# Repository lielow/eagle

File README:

Eagle file for IOT Project.

15/07/2559

Tong.

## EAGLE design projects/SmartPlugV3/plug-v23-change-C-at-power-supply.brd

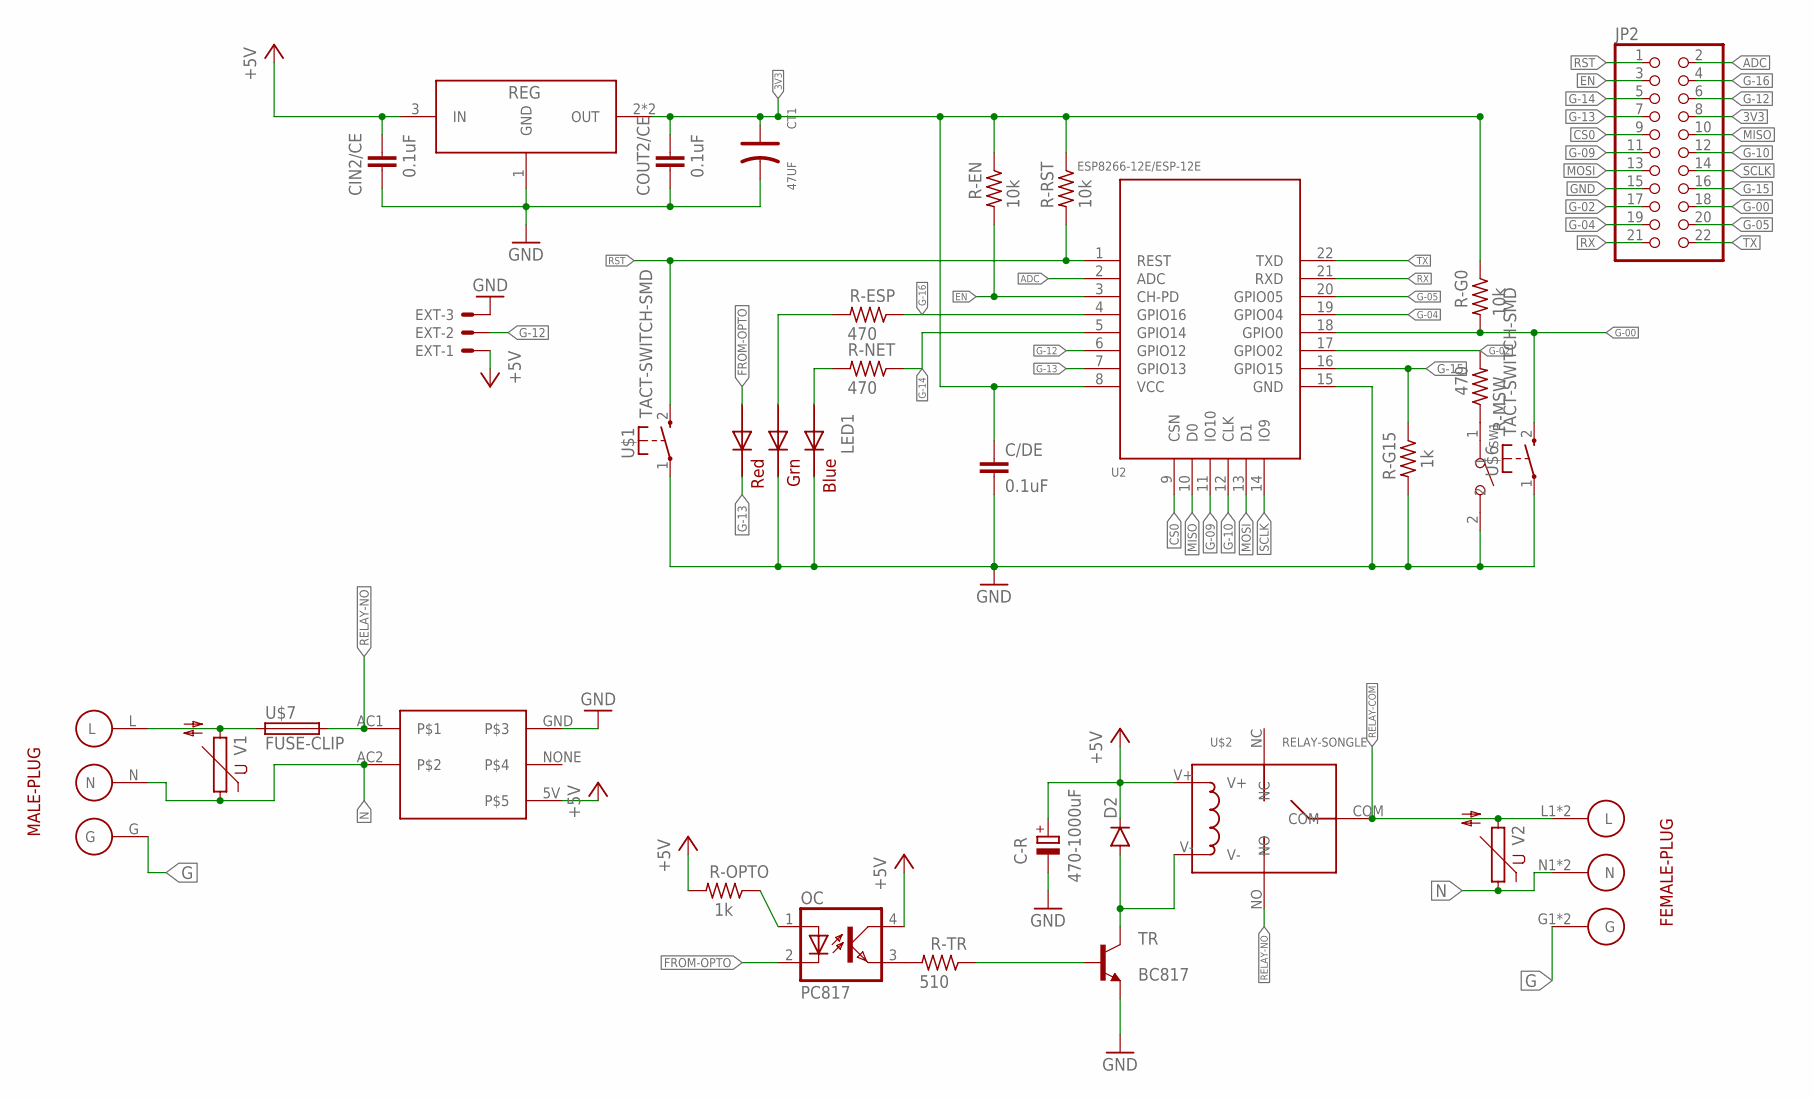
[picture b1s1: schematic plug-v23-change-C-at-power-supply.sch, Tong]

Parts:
C-R: 470-1000uF; E3,5-8
C/DE: 0.1uF; C0805
CIN2/CE: 0.1uF; C0805K
COUT2/CE: 0.1uF; C0805K
CT1: 47UF; ELECTRO-SMD-C-6MM
D2: DIODESOD123; SOD-123
EXT: 53048-03
JP2: PINHD-2X11; 2X11
LED1: RGBLED5050
OC: PC817; DIL04
R-EN: 10k; M0805
R-ESP: 470; M0805
R-G0: 10k; M0805
R-G15: 1k; M0805
R-MSW: 470; M0805
R-NET: 470; M0805
R-OPTO: 1k; M0805
R-RST: 10k; M0805
R-TR: 510; M0805
REG: AMS1117-3.3; SOT-223
SW1: DIP-BUTTON(2P-6.0X3.0X4.3MM)-TS-1101F; SW2-5.0-6.0X3.0X4.3MM
TR: BC817; SOT23-BEC
U2: ESP8266-12E/ESP-12E; LGA22-2.0-24X16MM
U$1, U$6: TACT-SWITCH-SMD
U$2: RELAY-SONGLE
U$3: MALE-PLUG
U$4: POWERSUPPLY-5V-700MA
U$5: FEMALE-PLUG
U$7: FUSE-CLIP
V1, V2: S14K11

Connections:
3V3: C/DE.1, COUT2/CE.1, CT1.+, JP2.8, R-EN.1, R-G0.1, R-RST.1, REG.2 (OUT), REG.4 (OUT), U2.8 (VCC)
+5V: C-R.+, CIN2/CE.1, D2.C, EXT.1, OC.4 (COL), R-OPTO.2, REG.3 (IN), U$2.V+, U$4.5V
ADC: JP2.2, U2.2 (ADC)
CS0: JP2.9, U2.9 (CSN)
EN: JP2.3, R-EN.2, U2.3 (CH-PD)
FROM-OPTO: LED1.2 (RED_A), OC.2 (C)
G: U$3.G, U$5.G1 (G), U$5.G2 (G)
G-00: JP2.18, R-G0.2, U2.18 (GPIO0), U$6.2 (S)
G-02: JP2.17, R-MSW.2, U2.17 (GPIO02)
G-04: JP2.19, U2.19 (GPIO04)
G-05: JP2.20, U2.20 (GPIO05)
G-09: JP2.11, U2.11 (IO10)
G-10: JP2.12, U2.12 (CLK)
G-12: EXT.2, JP2.6, U2.6 (GPIO12)
G-13: JP2.7, LED1.5 (RED_C), U2.7 (GPIO13)
G-14: JP2.5, R-NET.1, U2.5 (GPIO14)
G-15: JP2.16, R-G15.1, U2.16 (GPIO15)
G-16: JP2.4, R-ESP.1, U2.4 (GPIO16)
GND: C-R.-, C/DE.2, CIN2/CE.2, COUT2/CE.2, CT1.-, EXT.3, JP2.15, LED1.4 (BLUE_C), LED1.6 (GREEN_C), R-G15.2, REG.1 (GND), SW1.2, TR.E, U2.15 (GND), U$1.1, U$4.GND, U$6.1
LINE: U$3.L, U$7.3 (1), U$7.4 (1), V1.2
MISO: JP2.10, U2.10 (D0)
MOSI: JP2.13, U2.13 (D1)
N: U$3.N, U$4.AC2, U$5.N1 (N), U$5.N2 (N), V1.1, V2.1
unnamed: OC.3 (EMIT), R-TR.2
unnamed: R-TR.1, TR.B
unnamed: LED1.1 (GREEN_A), R-ESP.2
unnamed: LED1.3 (BLUE_A), R-NET.2
unnamed: OC.1 (A), R-OPTO.1
unnamed: D2.A, TR.C, U$2.V-
unnamed: R-MSW.1, SW1.1
RELAY-COM: U$2.COM, U$5.L1 (L), U$5.L2 (L), V2.2
RELAY-NO: U$2.NO, U$4.AC1, U$7.5 (2), U$7.6 (2)
RST: JP2.1, R-RST.2, U2.1 (REST), U$1.2 (S)
RX: JP2.21, U2.21 (RXD)
SCLK: JP2.14, U2.14 (IO9)
TX: JP2.22, U2.22 (TXD)

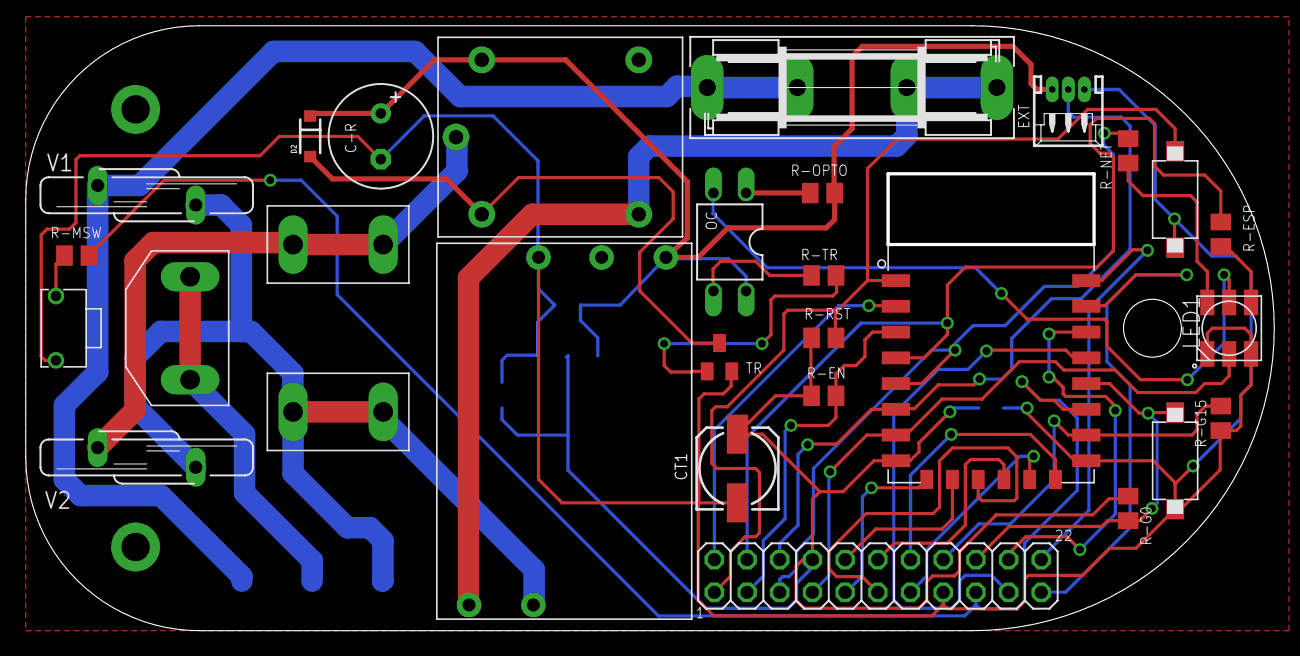
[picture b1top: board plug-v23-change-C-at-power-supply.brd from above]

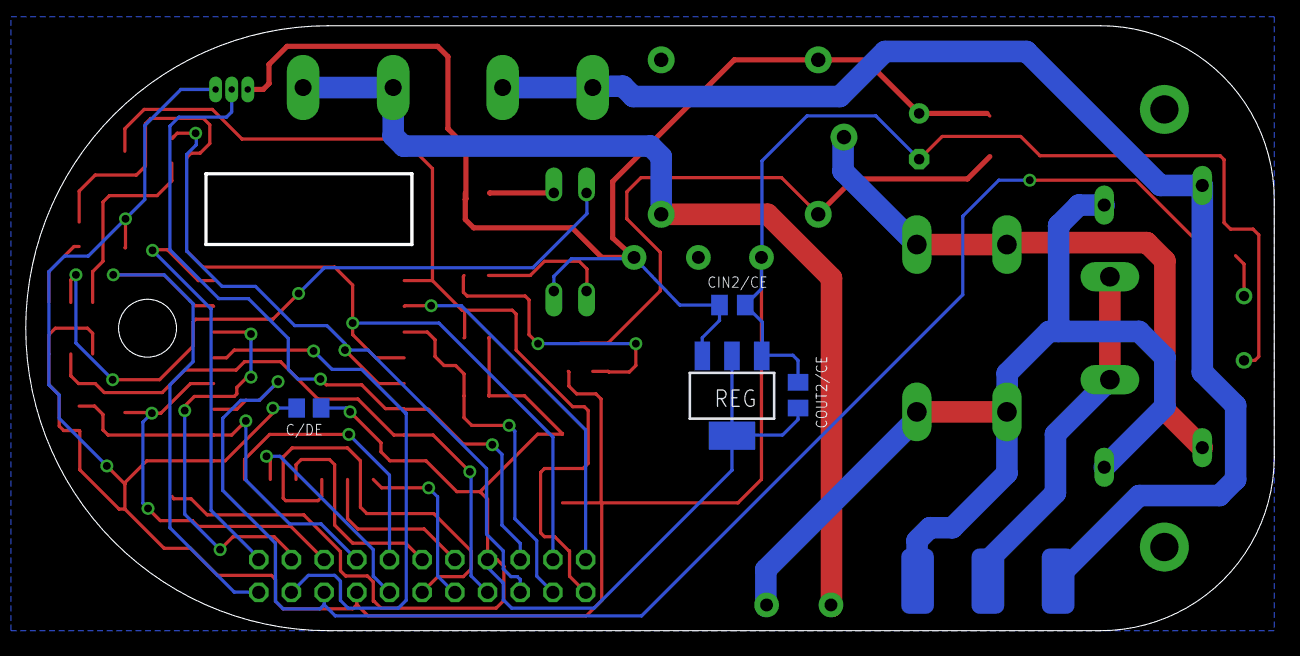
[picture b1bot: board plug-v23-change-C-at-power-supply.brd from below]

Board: 2 copper layers, 97.0 x 47.0 mm, 32 parts (5 on the bottom side), 36 nets.

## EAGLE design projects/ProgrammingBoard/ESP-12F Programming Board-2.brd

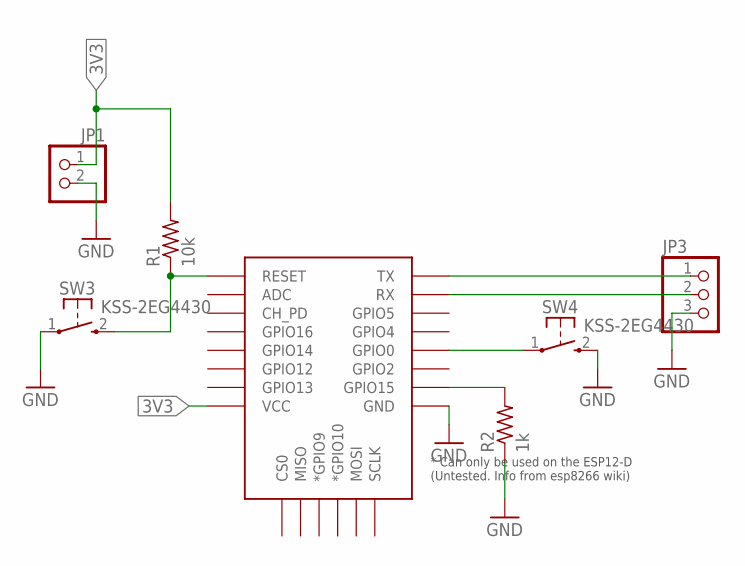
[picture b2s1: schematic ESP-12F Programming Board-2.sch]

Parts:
JP1: PINHD-1X2; 1X02
JP3: PINHD-1X3; 1X03
R1: 10k; R0805
R2: 1k; R0805
SW3, SW4: KSS-2EG4430
U1: ESP12ESMD; ESP12E-SMD

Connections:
3V3: JP1.1, R1.2, U1.VCC
GND: JP1.2, JP3.3, R2.1, SW3.1, SW4.2 (S), U1.GND
unnamed: R1.1, SW3.2 (S), U1.RESET
unnamed: JP3.2, U1.RXD0 (RX)
unnamed: JP3.1, U1.TXD0 (TX)
unnamed: SW4.1, U1.GPIO0
unnamed: R2.2, U1.GPIO15

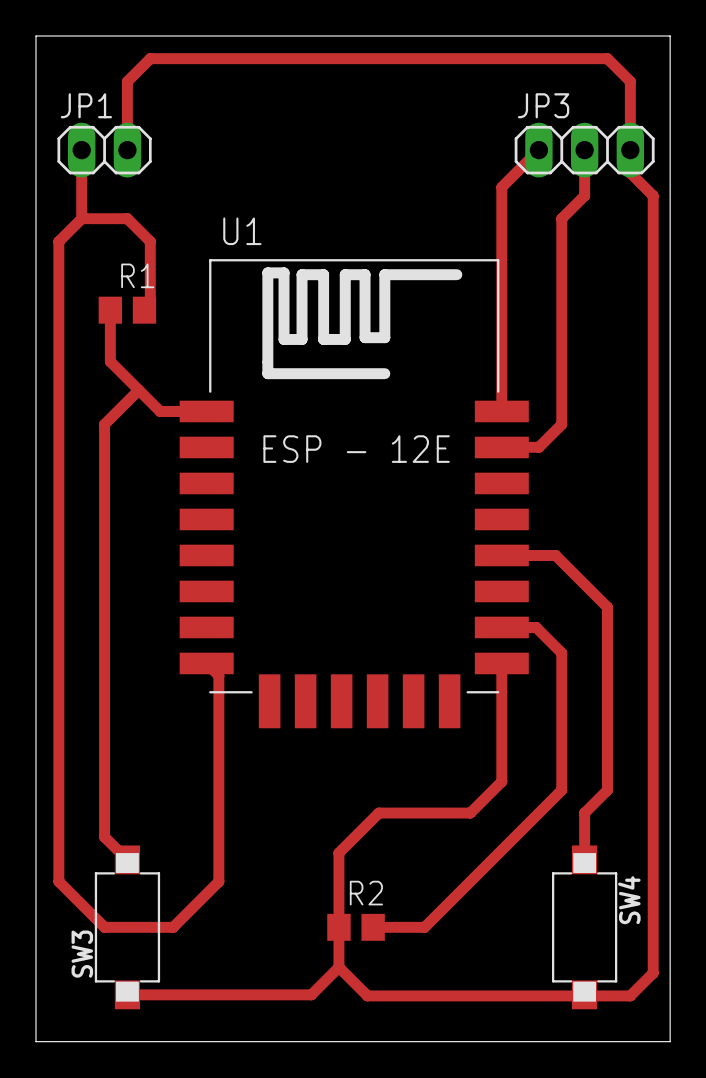
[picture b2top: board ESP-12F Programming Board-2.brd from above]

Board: 2 copper layers, 35.2 x 55.9 mm, 7 parts (0 on the bottom side), 7 nets.

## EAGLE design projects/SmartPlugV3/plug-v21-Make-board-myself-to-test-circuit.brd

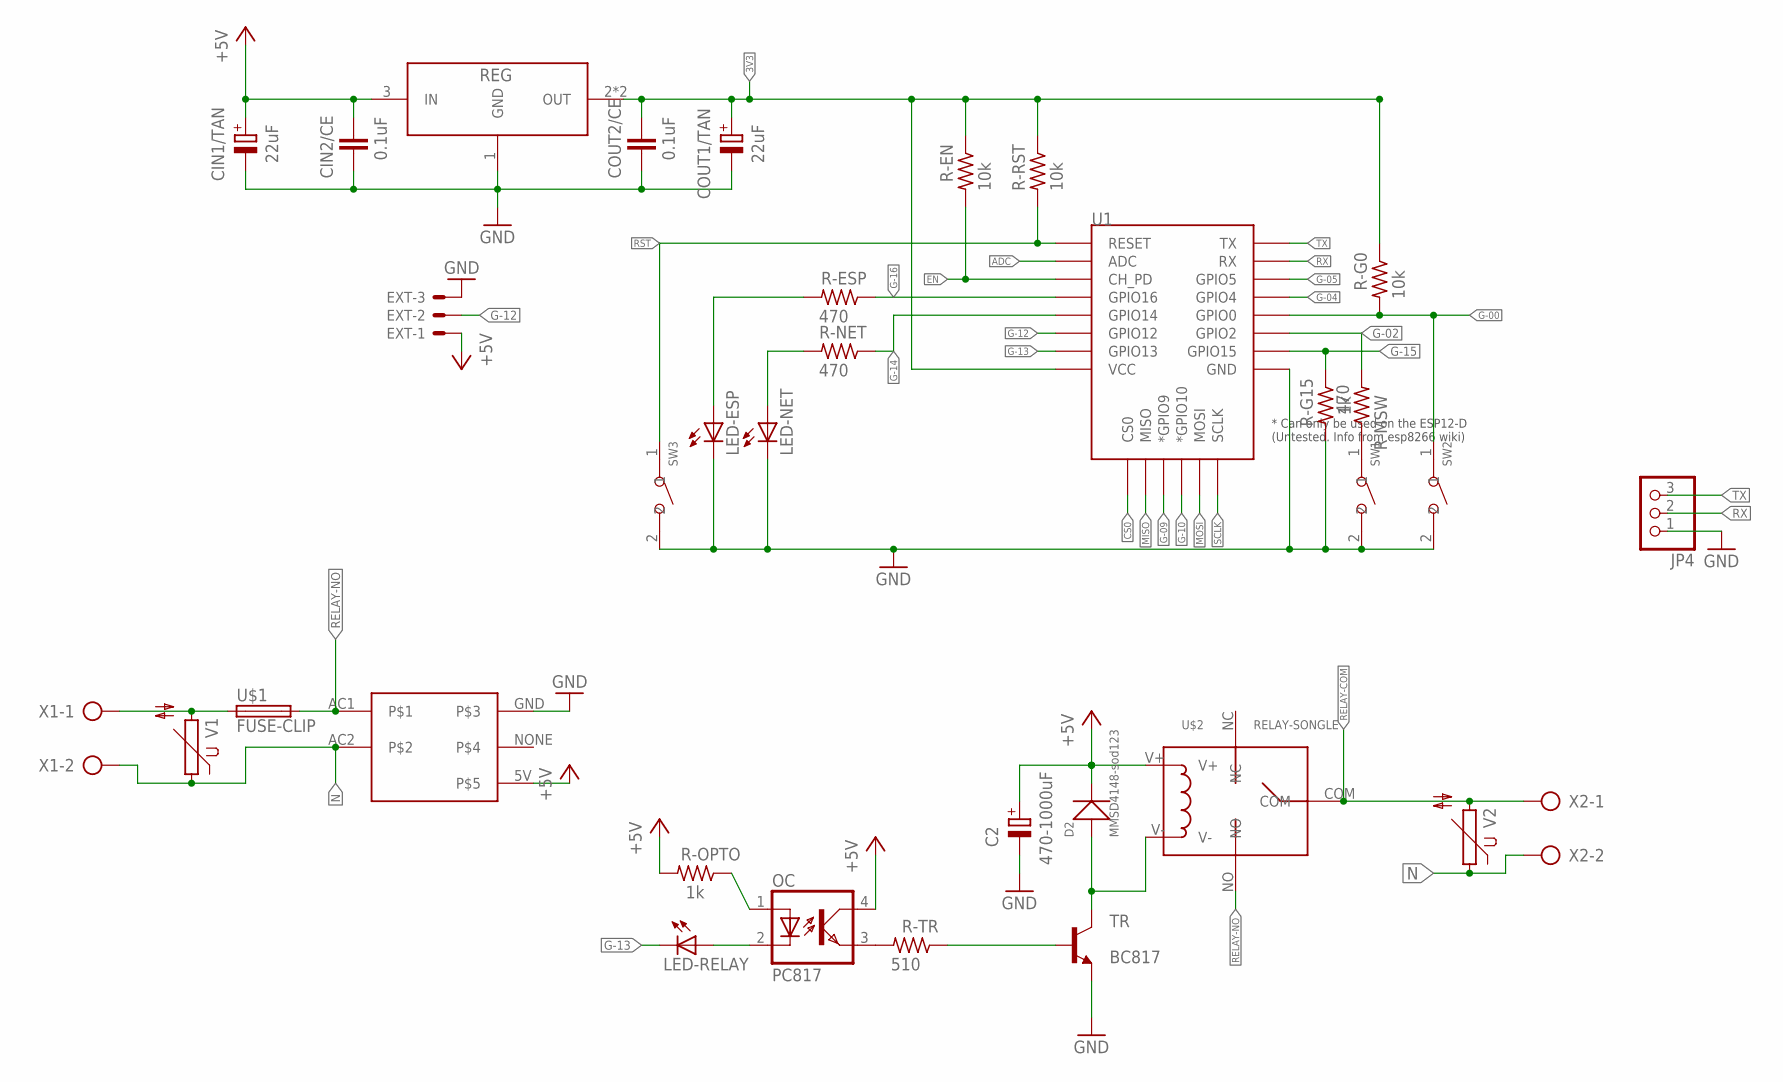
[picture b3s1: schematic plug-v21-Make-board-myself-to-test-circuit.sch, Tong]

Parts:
C2: 470-1000uF; E3,5-8
CIN1/TAN: 22uF; B/3528-21R
CIN2/CE: 0.1uF; C0805K
COUT1/TAN: 22uF; B/3528-21R
COUT2/CE: 0.1uF; C0805K
D2: MMSD4148-sod123; SOD-123
EXT: 53048-03
JP4: PINHD-1X3; 1X03
LED-ESP: LEDCHIPLED_0805; CHIPLED_0805
LED-NET: LEDCHIPLED_0805; CHIPLED_0805
LED-RELAY: LEDCHIPLED_0805; CHIPLED_0805
OC: PC817; DIL04
R-EN: 10k; M0805
R-ESP: 470; M0805
R-G0: 10k; M0805
R-G15: 1k; M0805
R-MSW: 470; M0805
R-NET: 470; M0805
R-OPTO: 1k; M0805
R-RST: 10k; M0805
R-TR: 510; M0805
REG: AMS1117-3.3; SOT-223
SW1, SW2, SW3: DIP-BUTTON(2P-6.0X3.0X4.3MM)-TS-1101F; SW2-5.0-6.0X3.0X4.3MM
TR: BC817; SOT23-BEC
U1: ESP12ESMD; ESP12E-SMD
U$1: FUSE-CLIP
U$2: RELAY-SONGLE
U$4: POWERSUPPLY-5V-700MA
V1, V2: S14K11
X1, X2: AK300/2

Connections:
3V3: COUT1/TAN.+, COUT2/CE.1, R-EN.1, R-G0.1, R-RST.1, REG.2 (OUT), REG.4 (OUT), U1.VCC
+5V: C2.+, CIN1/TAN.+, CIN2/CE.1, D2.-, EXT.1, OC.4 (COL), R-OPTO.2, REG.3 (IN), U$2.V+, U$4.5V
ADC: U1.ADC
CS0: U1.CS0
EN: R-EN.2, U1.CH_PD
G-00: R-G0.2, SW2.1, U1.GPIO0
G-02: R-MSW.2, U1.GPIO2
G-04: U1.GPIO4
G-05: U1.GPIO5
G-09: U1.GPIO9 (*GPIO9)
G-10: U1.GPIO10 (*GPIO10)
G-12: EXT.2, U1.GPIO12
G-13: LED-RELAY.C, U1.GPIO13
G-14: R-NET.1, U1.GPIO14
G-15: R-G15.1, U1.GPIO15
G-16: R-ESP.1, U1.GPIO16
GND: C2.-, CIN1/TAN.-, CIN2/CE.2, COUT1/TAN.-, COUT2/CE.2, EXT.3, JP4.1, LED-ESP.C, LED-NET.C, R-G15.2, REG.1 (GND), SW1.2, SW2.2, SW3.2, TR.E, U1.GND, U$4.GND
LINE: U$1.3 (1), U$1.4 (1), V1.2, X1.1
MISO: U1.MISO
MOSI: U1.MOSI
N: U$4.AC2, V1.1, V2.1, X1.2, X2.2
unnamed: OC.3 (EMIT), R-TR.2
unnamed: R-TR.1, TR.B
unnamed: LED-ESP.A, R-ESP.2
unnamed: OC.1 (A), R-OPTO.1
unnamed: LED-NET.A, R-NET.2
unnamed: D2.+, TR.C, U$2.V-
unnamed: LED-RELAY.A, OC.2 (C)
unnamed: R-MSW.1, SW1.1
RELAY-COM: U$2.COM, V2.2, X2.1
RELAY-NO: U$1.5 (2), U$1.6 (2), U$2.NO, U$4.AC1
RST: R-RST.2, SW3.1, U1.RESET
RX: JP4.2, U1.RXD0 (RX)
SCLK: U1.SCLK
TX: JP4.3, U1.TXD0 (TX)

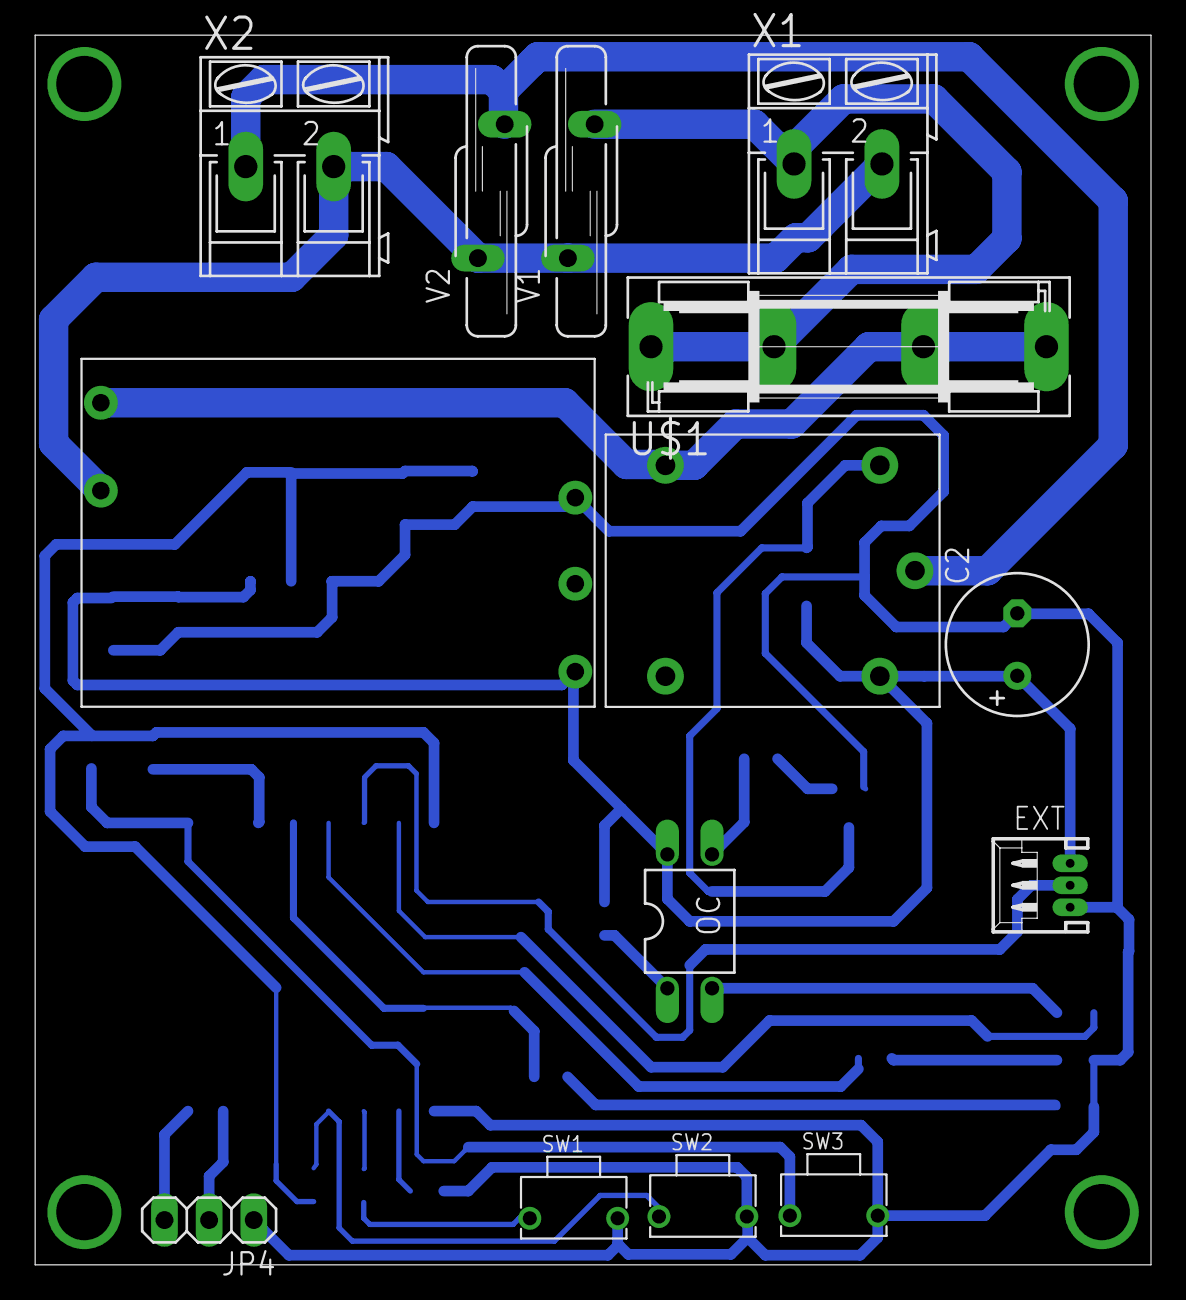
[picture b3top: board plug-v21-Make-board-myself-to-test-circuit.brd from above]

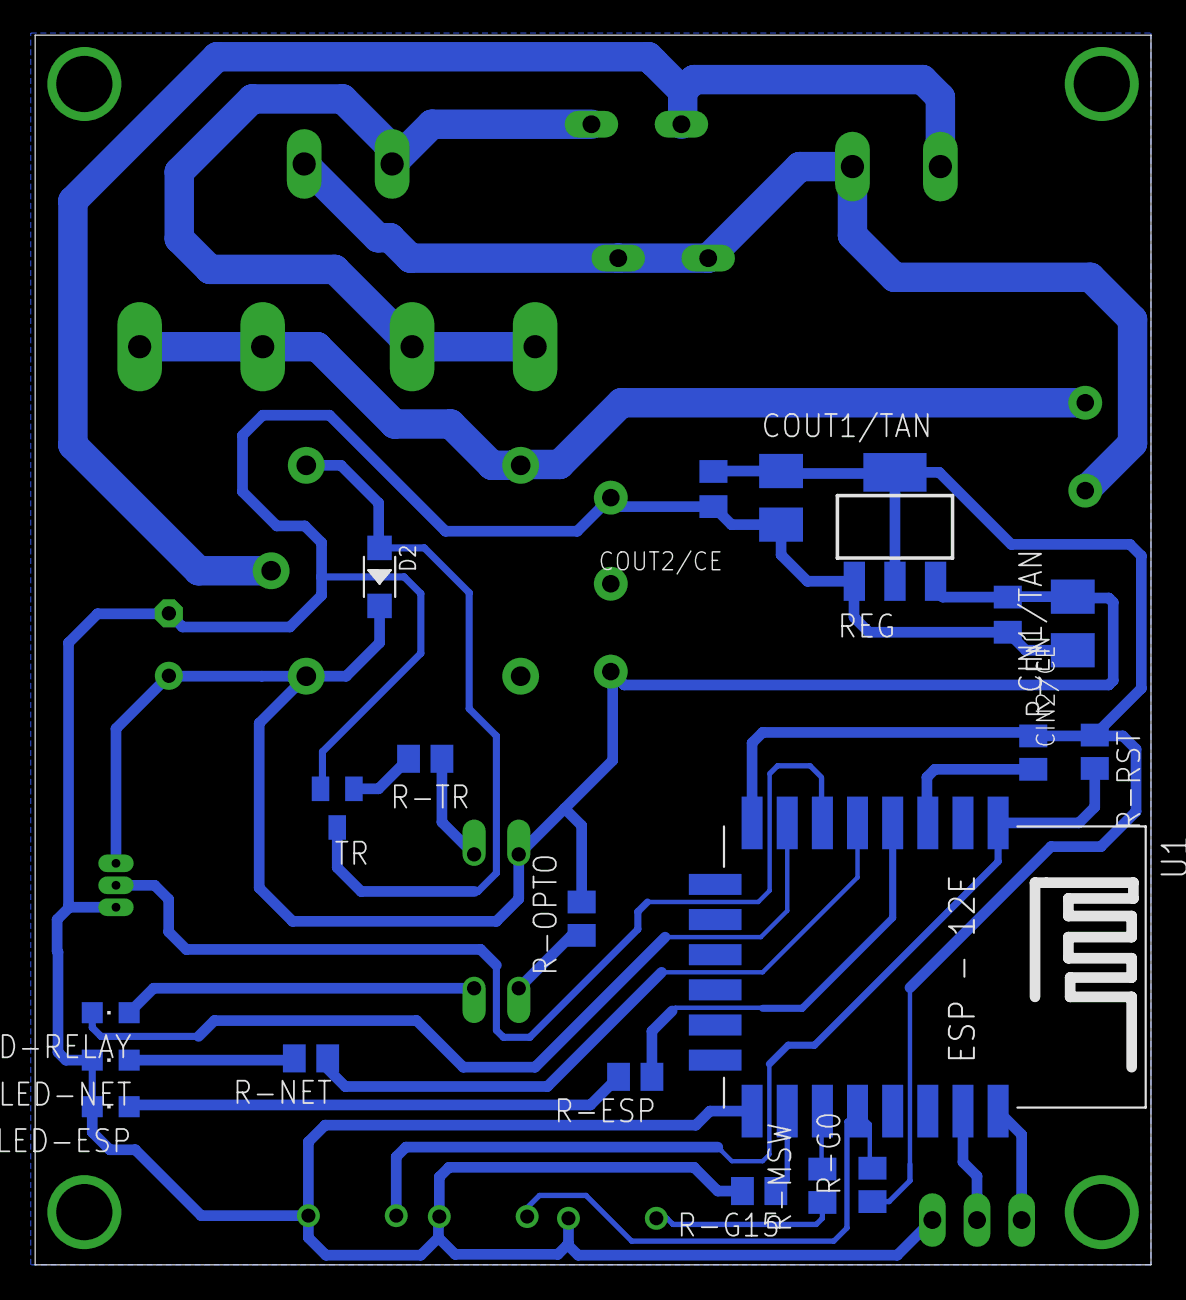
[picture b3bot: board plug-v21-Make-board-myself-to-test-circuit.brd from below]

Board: 2 copper layers, 63.5 x 70.0 mm, 34 parts (20 on the bottom side), 26 nets.

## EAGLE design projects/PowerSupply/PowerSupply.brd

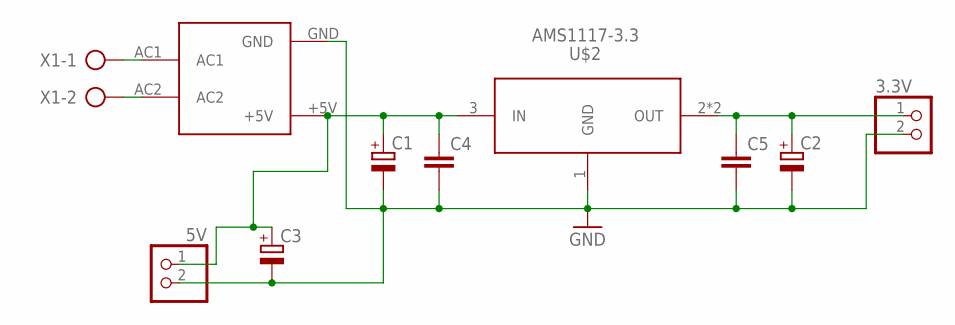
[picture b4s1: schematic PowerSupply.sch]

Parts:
3.3V, 5V: PINHD-1X2; 1X02
C1, C2: CPOL-EUB/3528-21R; B/3528-21R
C3: CPOL-EUE2-5; E2-5
C4, C5: C-EUC0805K; C0805K
U$1: HLK-PM01
U$2: AMS1117-3.3; SOT-223
X1: AK300/2

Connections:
GND: 3.3V.2, 5V.2, C1.-, C2.-, C3.-, C4.2, C5.2, U$1.GND, U$2.1 (GND)
unnamed: 5V.1, C1.+, C3.+, C4.1, U$1.+5V, U$2.3 (IN)
unnamed: 3.3V.1, C2.+, C5.1, U$2.2 (OUT), U$2.4 (OUT)
unnamed: U$1.AC1, X1.1
unnamed: U$1.AC2, X1.2

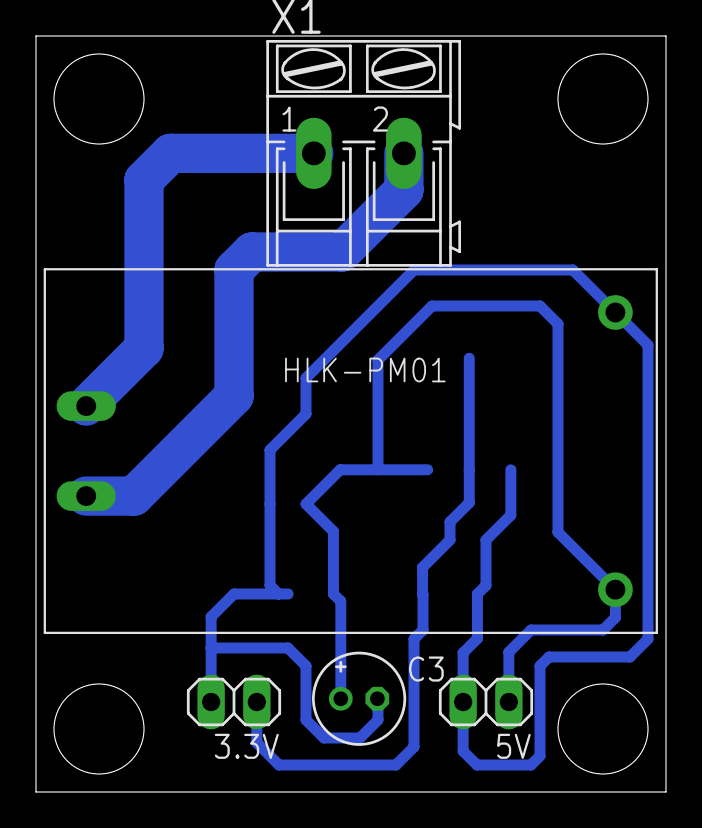
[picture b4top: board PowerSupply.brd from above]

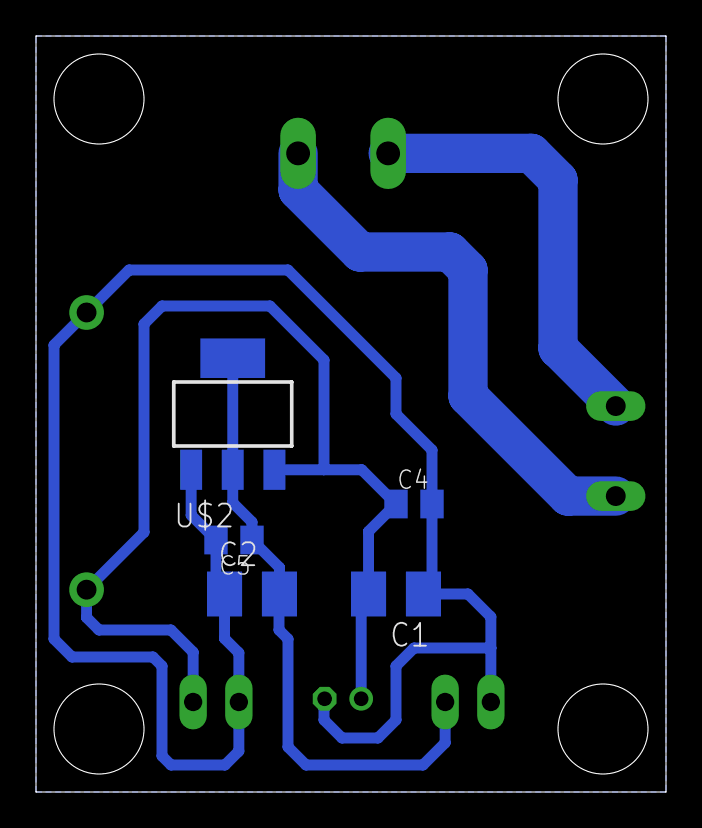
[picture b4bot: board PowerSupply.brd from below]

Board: 2 copper layers, 35.0 x 42.0 mm, 10 parts (5 on the bottom side), 5 nets.

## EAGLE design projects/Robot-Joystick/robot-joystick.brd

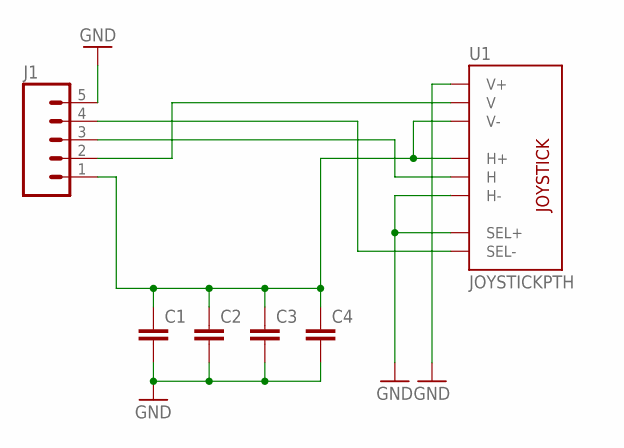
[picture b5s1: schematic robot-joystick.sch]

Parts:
C1, C2, C3, C4: C-EUC3216; C3216
J1: M05PTH; 1X05
U1: JOYSTICKPTH; JOYSTICK

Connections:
GND: C1.2, C2.2, C3.2, C4.2, J1.5, U1.B1A (SEL+), U1.H3 (H-), U1.V1 (V+)
unnamed: J1.4, U1.B2A (SEL-)
unnamed: J1.2, U1.V2 (V)
unnamed: J1.3, U1.H2 (H)
unnamed: C1.1, C2.1, C3.1, C4.1, J1.1, U1.H1 (H+), U1.V3 (V-)

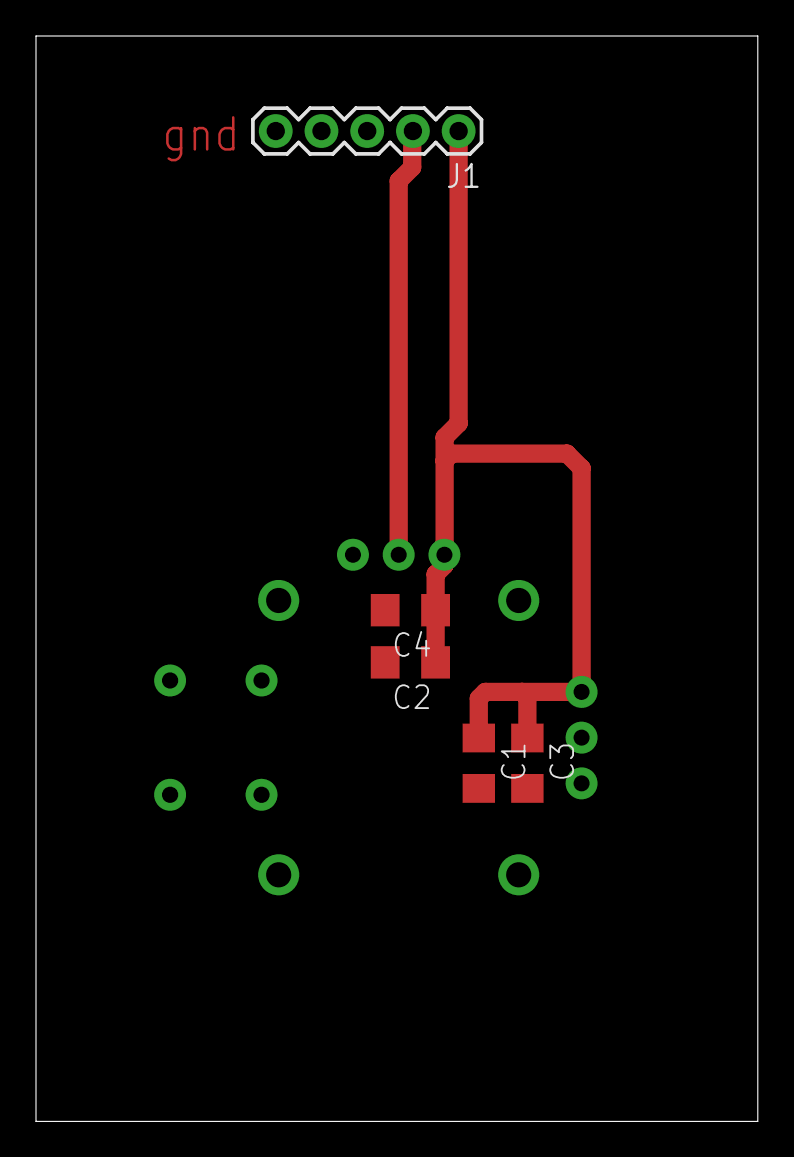
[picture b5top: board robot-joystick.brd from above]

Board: 2 copper layers, 40.1 x 60.3 mm, 6 parts (1 on the bottom side), 5 nets.

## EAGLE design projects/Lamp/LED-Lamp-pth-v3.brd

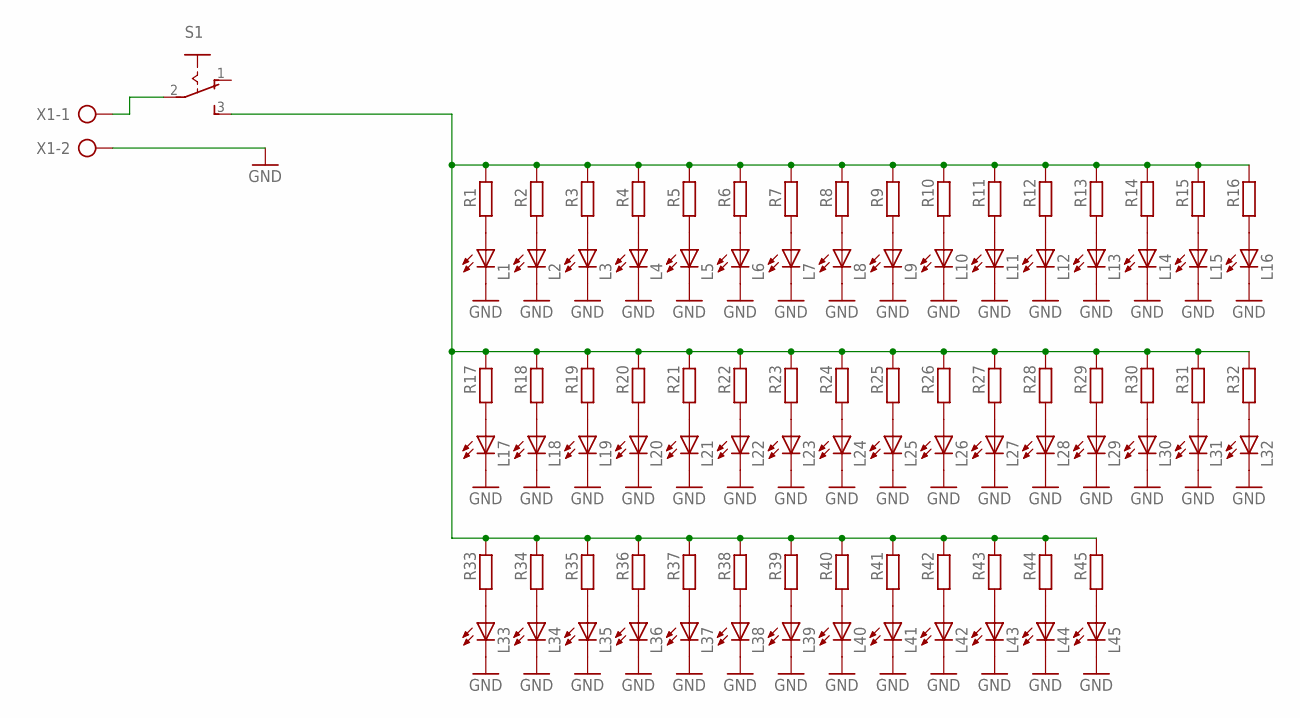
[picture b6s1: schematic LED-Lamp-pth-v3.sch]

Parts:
L1, L2, L3, L4, L5, L6, L7, L8, L9, L10, L11, L12, L13, L14, L15, L16, L17, L18, L19, L20, L21, L22, L23, L24, L25, L26, L27, L28, L29, L30, L31, L32, L33, L34, L35, L36, L37, L38, L39, L40, L41, L42, L43, L44, L45: LEDCHIP-LED0805; CHIP-LED0805
R1, R2, R3, R4, R5, R6, R7, R8, R9, R10, R11, R12, R13, R14, R15, R16, R17, R18, R19, R20, R21, R22, R23, R24, R25, R26, R27, R28, R29, R30, R31, R32, R33, R34, R35, R36, R37, R38, R39, R40, R41, R42, R43, R44, R45: R-EU_0207/7; 0207/7
S1: 255SB
X1: AK300/2

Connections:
GND: L1.C, L2.C, L3.C, L4.C, L5.C, L6.C, L7.C, L8.C, L9.C, L10.C, L11.C, L12.C, L13.C, L14.C, L15.C, L16.C, L17.C, L18.C, L19.C, L20.C, L21.C, L22.C, L23.C, L24.C, L25.C, L26.C, L27.C, L28.C, L29.C, L30.C, L31.C, L32.C, L33.C, L34.C, L35.C, L36.C, L37.C, L38.C, L39.C, L40.C, L41.C, L42.C, L43.C, L44.C, L45.C, X1.2
unnamed: L2.A, R2.1
unnamed: L3.A, R3.1
unnamed: L4.A, R4.1
unnamed: L5.A, R5.1
unnamed: L6.A, R6.1
unnamed: L7.A, R7.1
unnamed: L8.A, R8.1
unnamed: L9.A, R9.1
unnamed: L10.A, R10.1
unnamed: L11.A, R11.1
unnamed: L12.A, R12.1
unnamed: L13.A, R13.1
unnamed: L14.A, R14.1
unnamed: L15.A, R15.1
unnamed: L16.A, R16.1
unnamed: L17.A, R17.1
unnamed: L18.A, R18.1
unnamed: L19.A, R19.1
unnamed: L20.A, R20.1
unnamed: L21.A, R21.1
unnamed: L22.A, R22.1
unnamed: L23.A, R23.1
unnamed: L24.A, R24.1
unnamed: L25.A, R25.1
unnamed: L26.A, R26.1
unnamed: L27.A, R27.1
unnamed: S1.2, X1.1
unnamed: L28.A, R28.1
unnamed: L31.A, R31.1
unnamed: L29.A, R29.1
unnamed: L1.A, R1.1
unnamed: L30.A, R30.1
unnamed: L32.A, R32.1
unnamed: L33.A, R33.1
unnamed: L34.A, R34.1
unnamed: L35.A, R35.1
unnamed: L36.A, R36.1
unnamed: L37.A, R37.1
unnamed: L38.A, R38.1
unnamed: L39.A, R39.1
unnamed: L40.A, R40.1
unnamed: L41.A, R41.1
unnamed: L42.A, R42.1
unnamed: L43.A, R43.1
unnamed: L44.A, R44.1
unnamed: L45.A, R45.1
unnamed: R1.2, R2.2, R3.2, R4.2, R5.2, R6.2, R7.2, R8.2, R9.2, R10.2, R11.2, R12.2, R13.2, R14.2, R15.2, R16.2, R17.2, R18.2, R19.2, R20.2, R21.2, R22.2, R23.2, R24.2, R25.2, R26.2, R27.2, R28.2, R29.2, R30.2, R31.2, R32.2, R33.2, R34.2, R35.2, R36.2, R37.2, R38.2, R39.2, R40.2, R41.2, R42.2, R43.2, R44.2, R45.2, S1.3 (S)

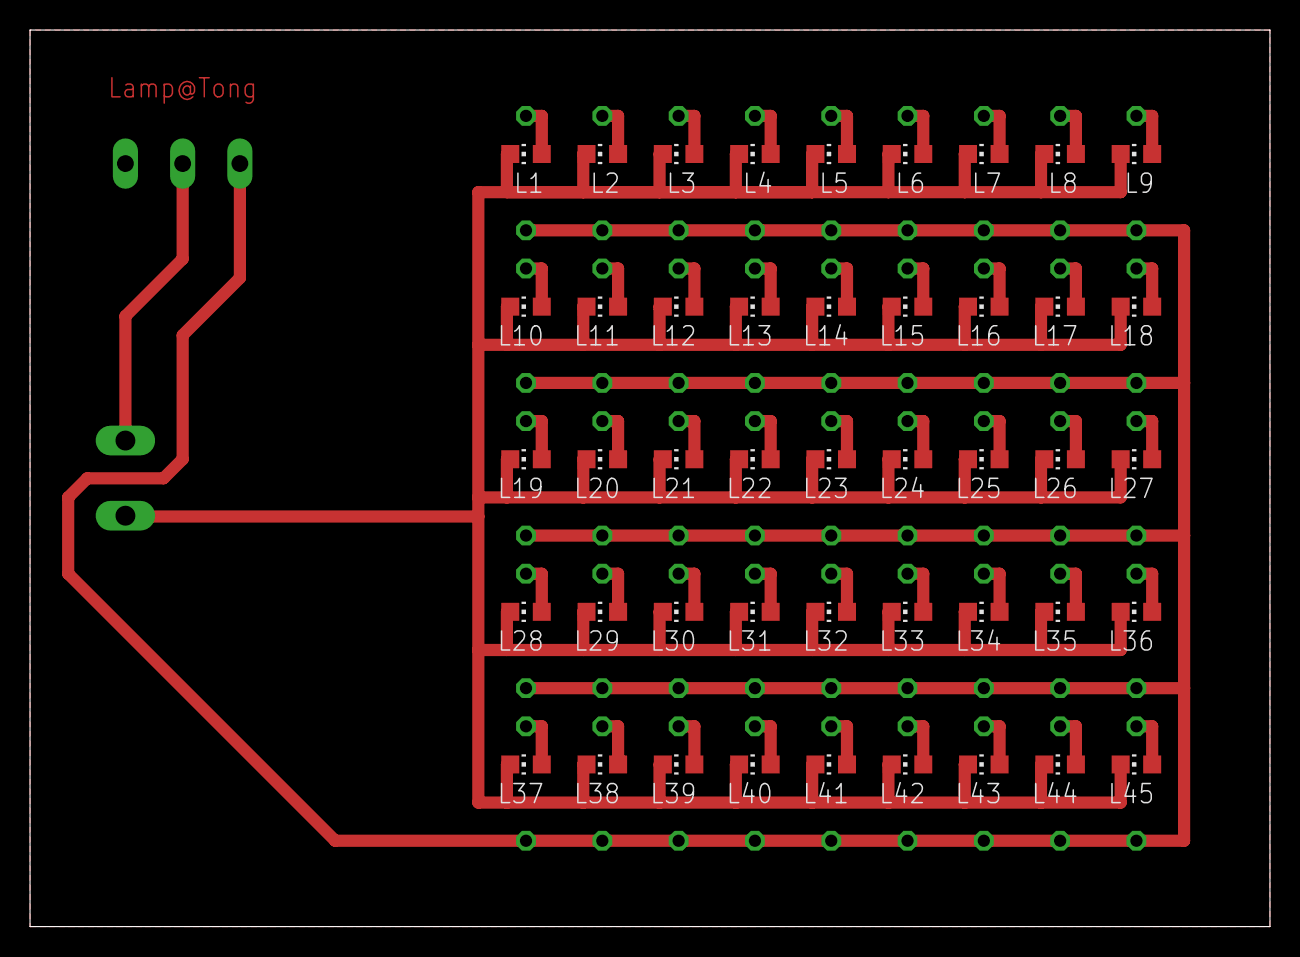
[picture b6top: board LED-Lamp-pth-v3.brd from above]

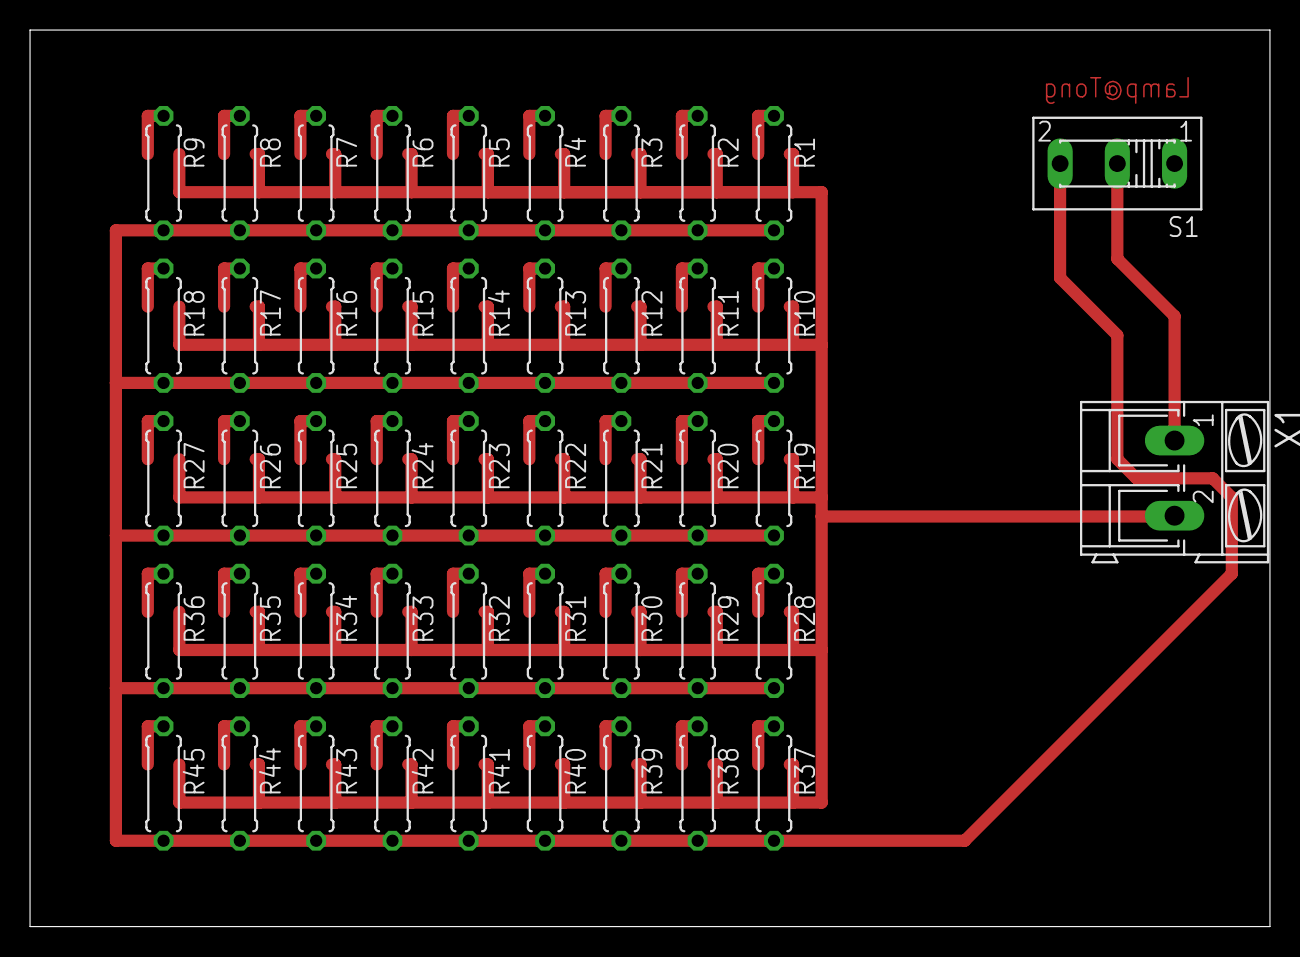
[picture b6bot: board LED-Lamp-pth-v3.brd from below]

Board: 2 copper layers, 82.5 x 59.7 mm, 92 parts (47 on the bottom side), 48 nets.

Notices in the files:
parts and their libraries:
SparkFun-Electromechanical: Licensing: Creative Commons ShareAlike 4.0 International - https://creativecommons.org/licenses/by-sa/4.0
